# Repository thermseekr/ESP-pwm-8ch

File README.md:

# ESP-PWM-8CH
 
ESP8266/ESP32 based board with 8x PWM output channels.

This board is designed to be driven by an Olimex ESP32-POE, ESP32-POE-ISO or Wemos D1 Mini modules. When using the Wemos D1 Mini the maximum number of outputs is 4, and expect some flickering and frequency oscillation due to the software implementation of the PWMs.

The design considers that the board will be mounted on a PCB DIN rail holder. The dimensions consider the holders offered by the Brazilian manufacturer Metaltex, check [here](https://www.metaltex.com.br/produtos/componentes/suportes/sp7-suporte-para-montagem-de-placa-de-circuito-impresso-em-trilho-din) for details.

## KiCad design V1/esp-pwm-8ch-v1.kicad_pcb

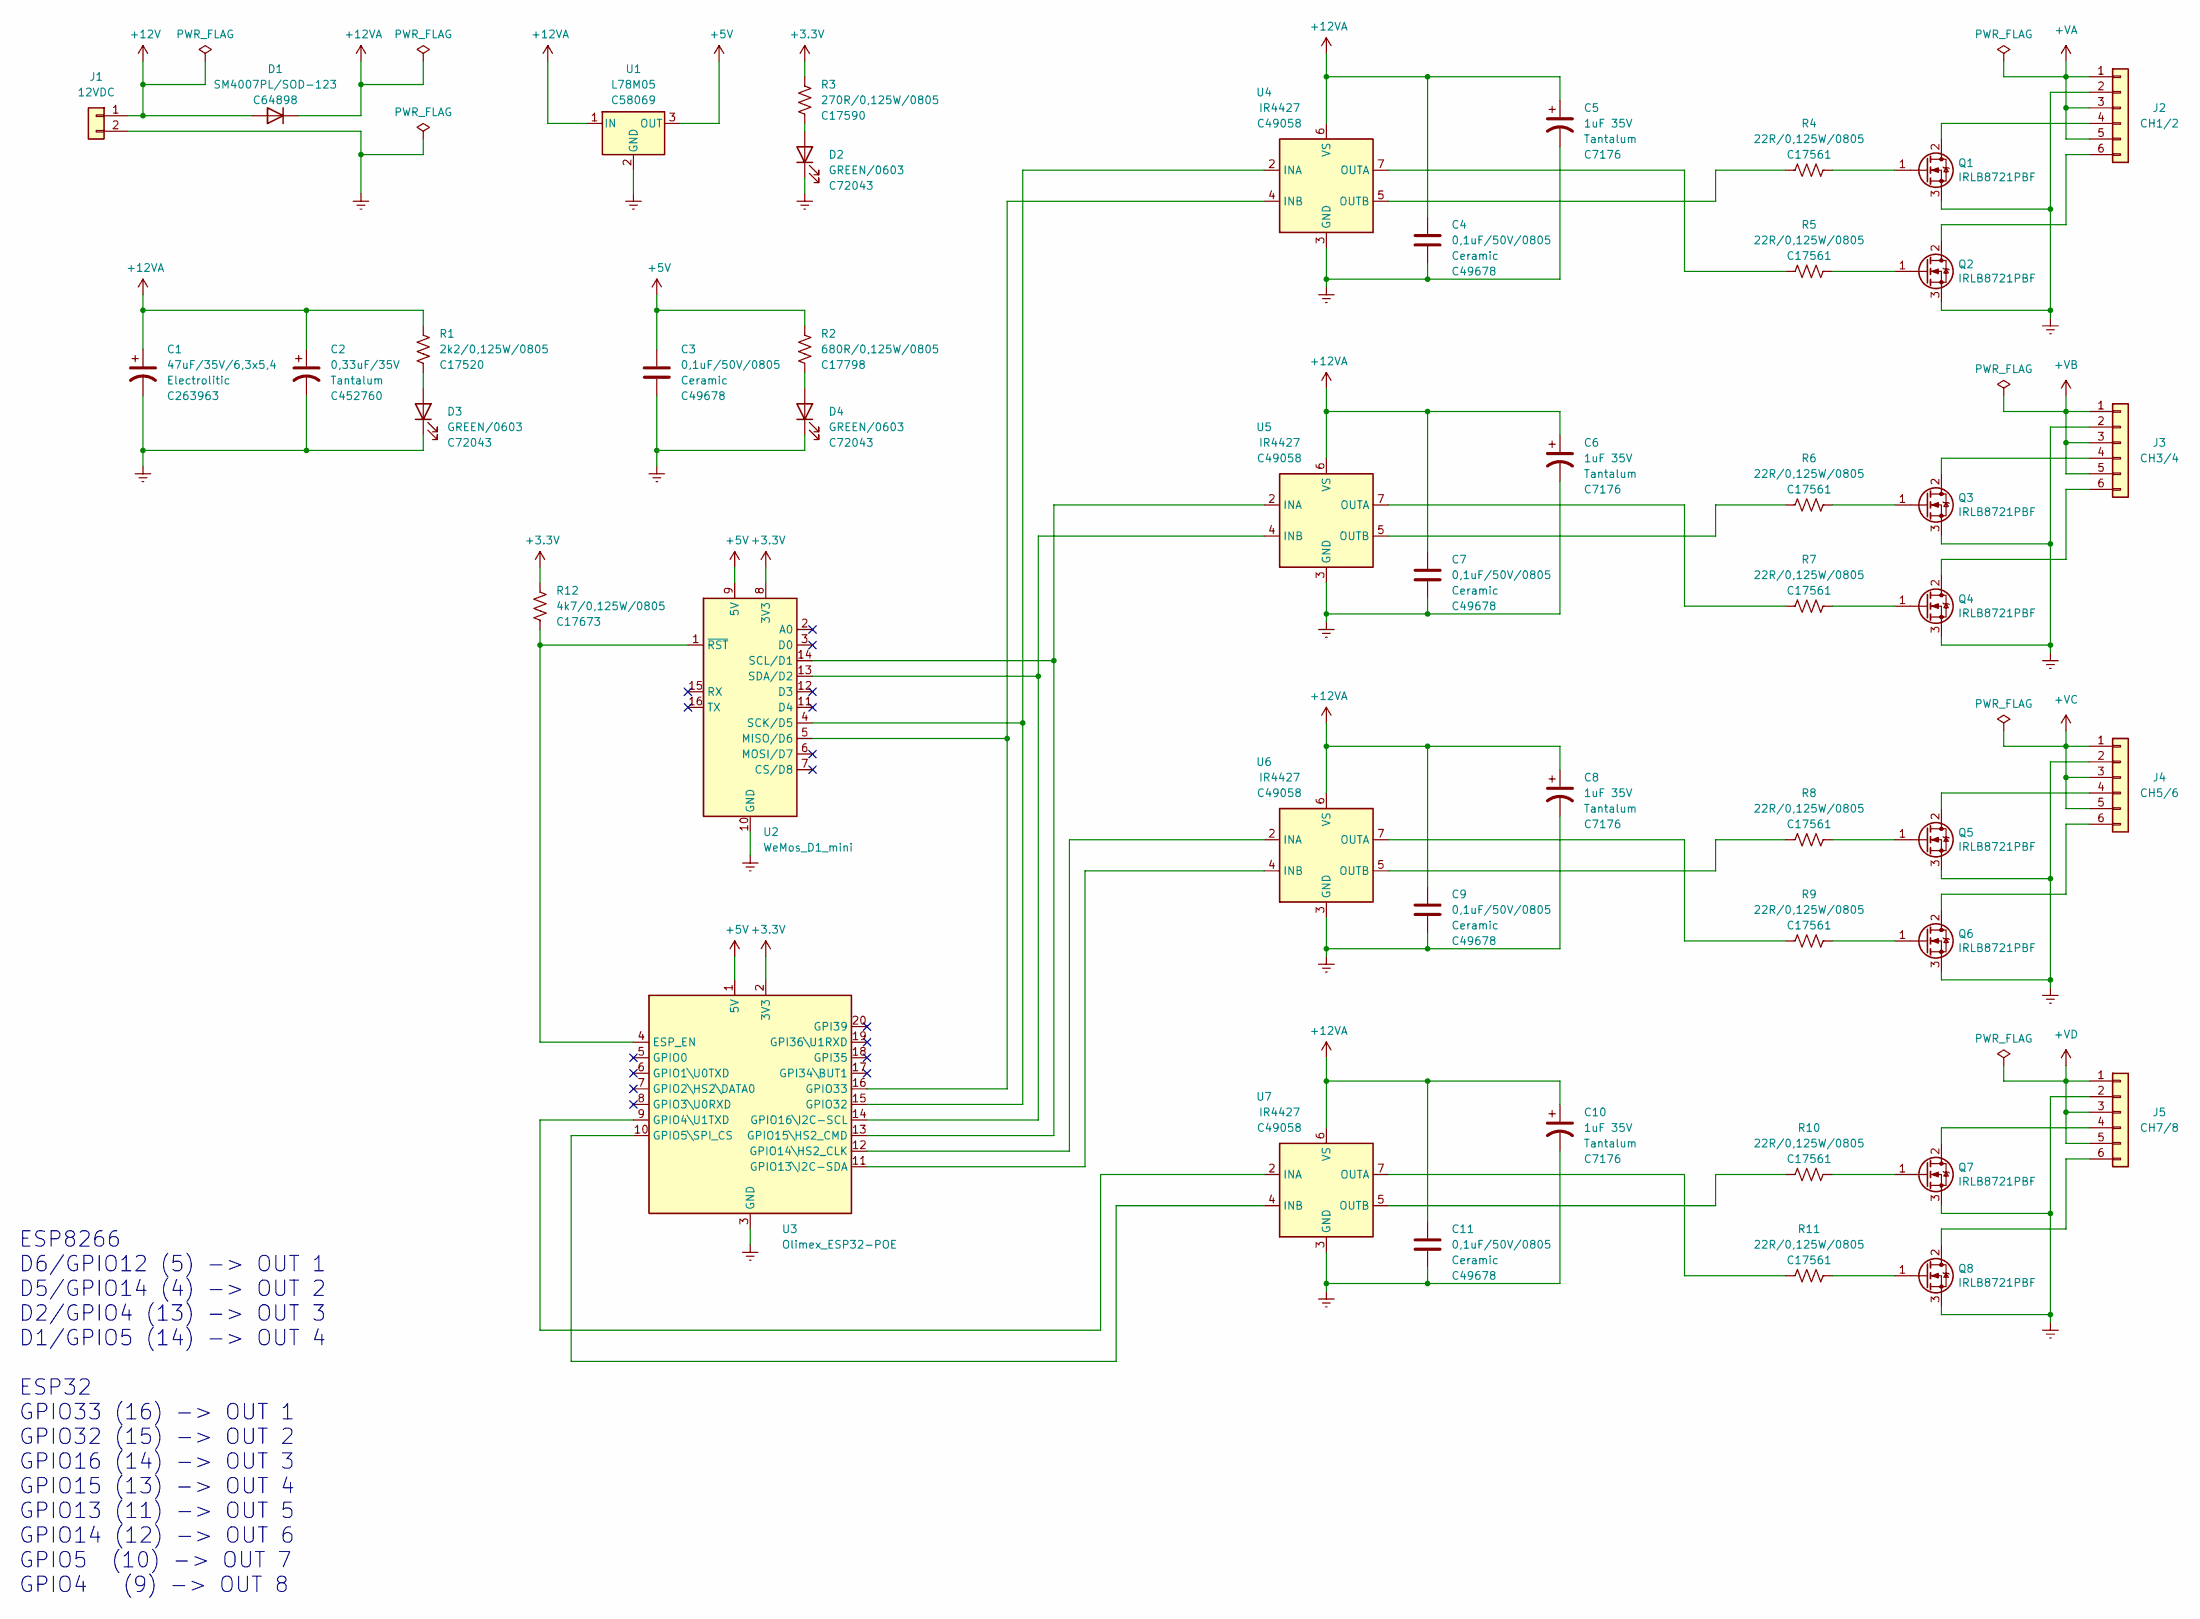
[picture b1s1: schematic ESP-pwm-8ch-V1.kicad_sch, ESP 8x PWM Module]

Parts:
C1: 47uF/35V/6,3x5,4; CP_Elec_6.3x5.4; Mfr PN CK1V470MCRE54; JLCPCB BOM 1
C2: 0,33uF/35V; CP_EIA-3216-18_Kemet-A_Pad1.58x1.35mm_HandSolder; Mfr PN T491A334M035AT; JLCPCB BOM 1
C3, C4, C7, C9, C11: 0,1uF/50V/0805; C_0805_2012Metric; Mfr PN CC0805KRX7R9BB104; JLCPCB BOM 1
C5, C6, C8, C10: 1uF 35V; CP_EIA-3216-18_Kemet-A_Pad1.58x1.35mm_HandSolder; Mfr PN TAJA105K035RNJ; JLCPCB BOM 1
D1: SM4007PL/SOD-123; D_SOD-123; Mfr PN SM4007PL; JLCPCB BOM 1
D2, D3, D4: GREEN/0603; LED_0603_1608Metric; Mfr PN 19-217/GHC-YR1S2/3T; JLCPCB BOM 1
J1: 12VDC; TerminalBlock_Phoenix_MKDS-3-2-5.08_1x02_P5.08mm_Horizontal; Mfr PN BR902V; JLCPCB BOM 0
J2: CH1/2; TerminalBlock_Phoenix_MKDS-3-6-5.08_1x06_P5.08mm_Horizontal; Mfr PN BR902V; JLCPCB BOM 0
J3: CH3/4; TerminalBlock_Phoenix_MKDS-3-6-5.08_1x06_P5.08mm_Horizontal; Mfr PN BR902V; JLCPCB BOM 0
J4: CH5/6; TerminalBlock_Phoenix_MKDS-3-6-5.08_1x06_P5.08mm_Horizontal; Mfr PN BR902V; JLCPCB BOM 0
J5: CH7/8; TerminalBlock_Phoenix_MKDS-3-6-5.08_1x06_P5.08mm_Horizontal; Mfr PN BR902V; JLCPCB BOM 0
Q1, Q2, Q3, Q4, Q5, Q6, Q7, Q8: IRLB8721PBF; TO-220-3_Vertical; Mfr PN IRLB8721PBF; JLCPCB BOM 0
R1: 2k2/0,125W/0805; R_0805_2012Metric; Mfr PN 0805W8F2201T5E; JLCPCB BOM 1
R2: 680R/0,125W/0805; R_0805_2012Metric; Mfr PN 0805W8F6800T5E; JLCPCB BOM 1
R3: 270R/0,125W/0805; R_0805_2012Metric; Mfr PN 0805W8F2700T5E; JLCPCB BOM 1
R4, R5, R6, R7, R8, R9, R10, R11: 22R/0,125W/0805; R_0805_2012Metric; Mfr PN 0805W8F220JT5E; JLCPCB BOM 1
R12: 4k7/0,125W/0805; R_0805_2012Metric; Mfr PN 0805W8F2201T5E; JLCPCB BOM 1
U1: L78M05; TO-252-2; Mfr PN L78M05ABDT-TR; JLCPCB BOM 1
U2: WeMos_D1_mini; WEMOS_D1_mini_light_pads
U3: Olimex_ESP32-POE; Olimex_ESP32-POE_Pads; Mfr PN ESP32-POE; JLCPCB BOM 0
U4, U5, U6, U7: IR4427; SOIC-8_3.9x4.9mm_P1.27mm; Mfr PN IR4427STRPBF; JLCPCB BOM 1

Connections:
+3V3: R3.1, R12.1, U2.8 (3V3), U3.2 (3V3)
+5V: C3.1, R2.1, U1.3 (OUT), U2.9 (5V), U3.1 (5V)
+12V: D1.2 (A), J1.1
+12VA: C1.1, C2.1, C4.1, C5.1, C6.1, C7.1, C8.1, C9.1, C10.1, C11.1, D1.1 (K), R1.1, U1.1 (IN), U4.6 (VS), U5.6 (VS), U6.6 (VS), U7.6 (VS)
+VA: J2.1, J2.3, J2.5
+VB: J3.1, J3.3, J3.5
+VC: J4.1, J4.3, J4.5
+VD: J5.1, J5.3, J5.5
GNDREF: C1.2, C2.2, C3.2, C4.2, C5.2, C6.2, C7.2, C8.2, C9.2, C10.2, C11.2, D2.1 (K), D3.1 (K), D4.1 (K), J1.2, J2.2, J3.2, J4.2, J5.2, Q1.3 (S), Q2.3 (S), Q3.3 (S), Q4.3 (S), Q5.3 (S), Q6.3 (S), Q7.3 (S), Q8.3 (S), U1.2 (GND), U2.10 (GND), U3.3 (GND), U4.3 (GND), U5.3 (GND), U6.3 (GND), U7.3 (GND)
unnamed: D2.2 (A), R3.2
unnamed: D3.2 (A), R1.2
unnamed: D4.2 (A), R2.2
unnamed: J2.4, Q1.2 (D)
unnamed: J2.6, Q2.2 (D)
unnamed: J3.4, Q3.2 (D)
unnamed: J3.6, Q4.2 (D)
unnamed: J4.4, Q5.2 (D)
unnamed: J4.6, Q6.2 (D)
unnamed: J5.4, Q7.2 (D)
unnamed: J5.6, Q8.2 (D)
unnamed: Q1.1 (G), R4.1
unnamed: Q2.1 (G), R5.1
unnamed: Q3.1 (G), R6.1
unnamed: Q4.1 (G), R7.1
unnamed: Q5.1 (G), R8.1
unnamed: Q6.1 (G), R9.1
unnamed: Q7.1 (G), R10.1
unnamed: Q8.1 (G), R11.1
unnamed: R4.2, U4.5 (OUTB)
unnamed: R5.2, U4.7 (OUTA)
unnamed: R6.2, U5.5 (OUTB)
unnamed: R7.2, U5.7 (OUTA)
unnamed: R8.2, U6.5 (OUTB)
unnamed: R9.2, U6.7 (OUTA)
unnamed: R10.2, U7.5 (OUTB)
unnamed: R11.2, U7.7 (OUTA)
unnamed: R12.2, U2.1 (~RST), U3.4 (ESP_EN)
unnamed: U2.4 (SCK/D5), U3.15 (GPIO32), U4.2 (INA)
unnamed: U2.5 (MISO/D6), U3.16 (GPIO33), U4.4 (INB)
unnamed: U2.13 (SDA/D2), U3.14 (GPIO16\I2C-SCL), U5.4 (INB)
unnamed: U2.14 (SCL/D1), U3.13 (GPIO15\HS2_CMD), U5.2 (INA)
unnamed: U3.9 (GPIO4\U1TXD), U7.2 (INA)
unnamed: U3.10 (GPIO5\SPI_CS), U7.4 (INB)
unnamed: U3.11 (GPIO13\I2C-SDA), U6.4 (INB)
unnamed: U3.12 (GPIO14\HS2_CLK), U6.2 (INA)

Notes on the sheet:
ESP8266 D6/GPIO12 (5) -> OUT 1 D5/GPIO14 (4) -> OUT 2 D2/GPIO4 (13) -> OUT 3 D1/GPIO5 (14) -> OUT 4 ESP32 GPIO33 (16) -> OUT 1 GPIO32 (15) -> OUT 2 GPIO16 (14) -> OUT 3 GPIO15 (13) -> OUT 4 GPIO13 (11) -> OUT 5 GPIO14 (12) -> OUT 6 GPIO5 (10) -> OUT 7 GPIO4 (9) -> OUT 8

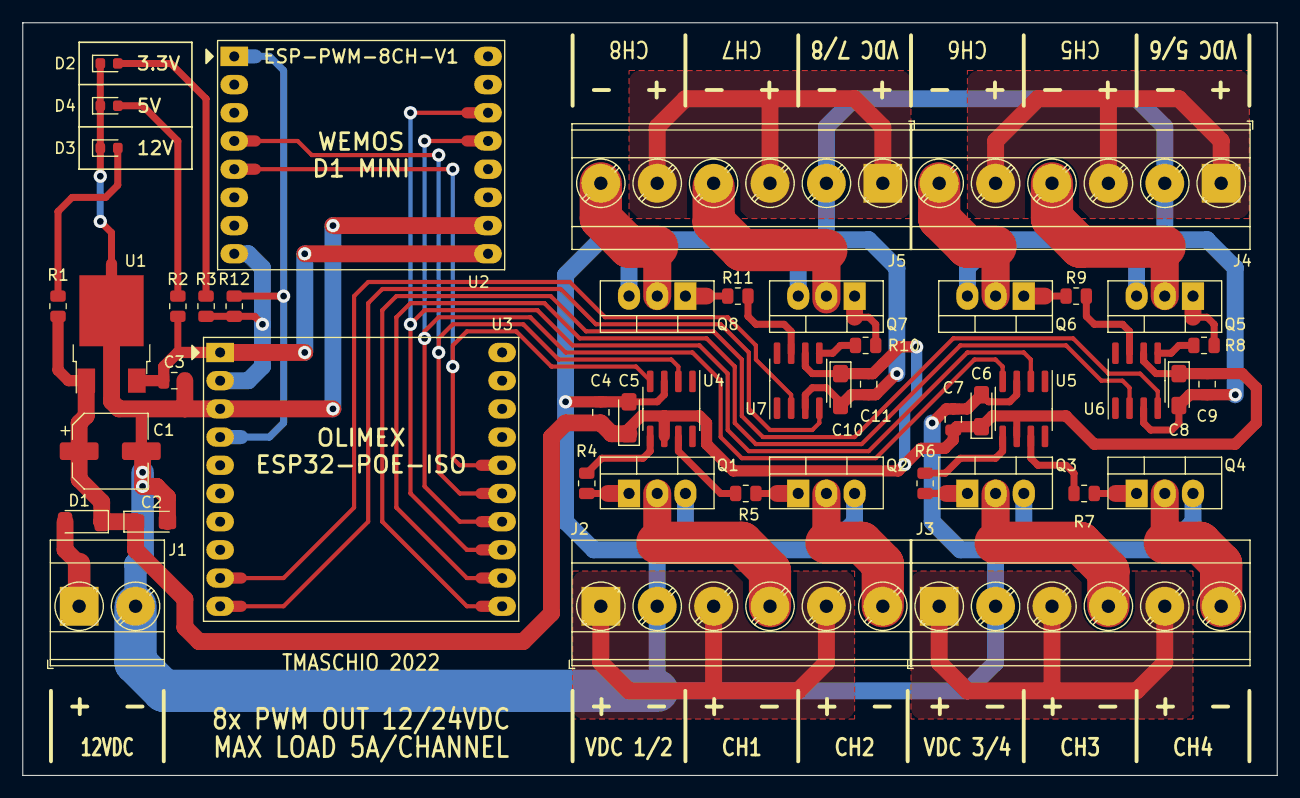
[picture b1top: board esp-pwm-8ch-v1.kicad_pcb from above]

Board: 2 copper layers, 113.0 x 67.8 mm, 47 parts (0 on the bottom side), 45 nets.

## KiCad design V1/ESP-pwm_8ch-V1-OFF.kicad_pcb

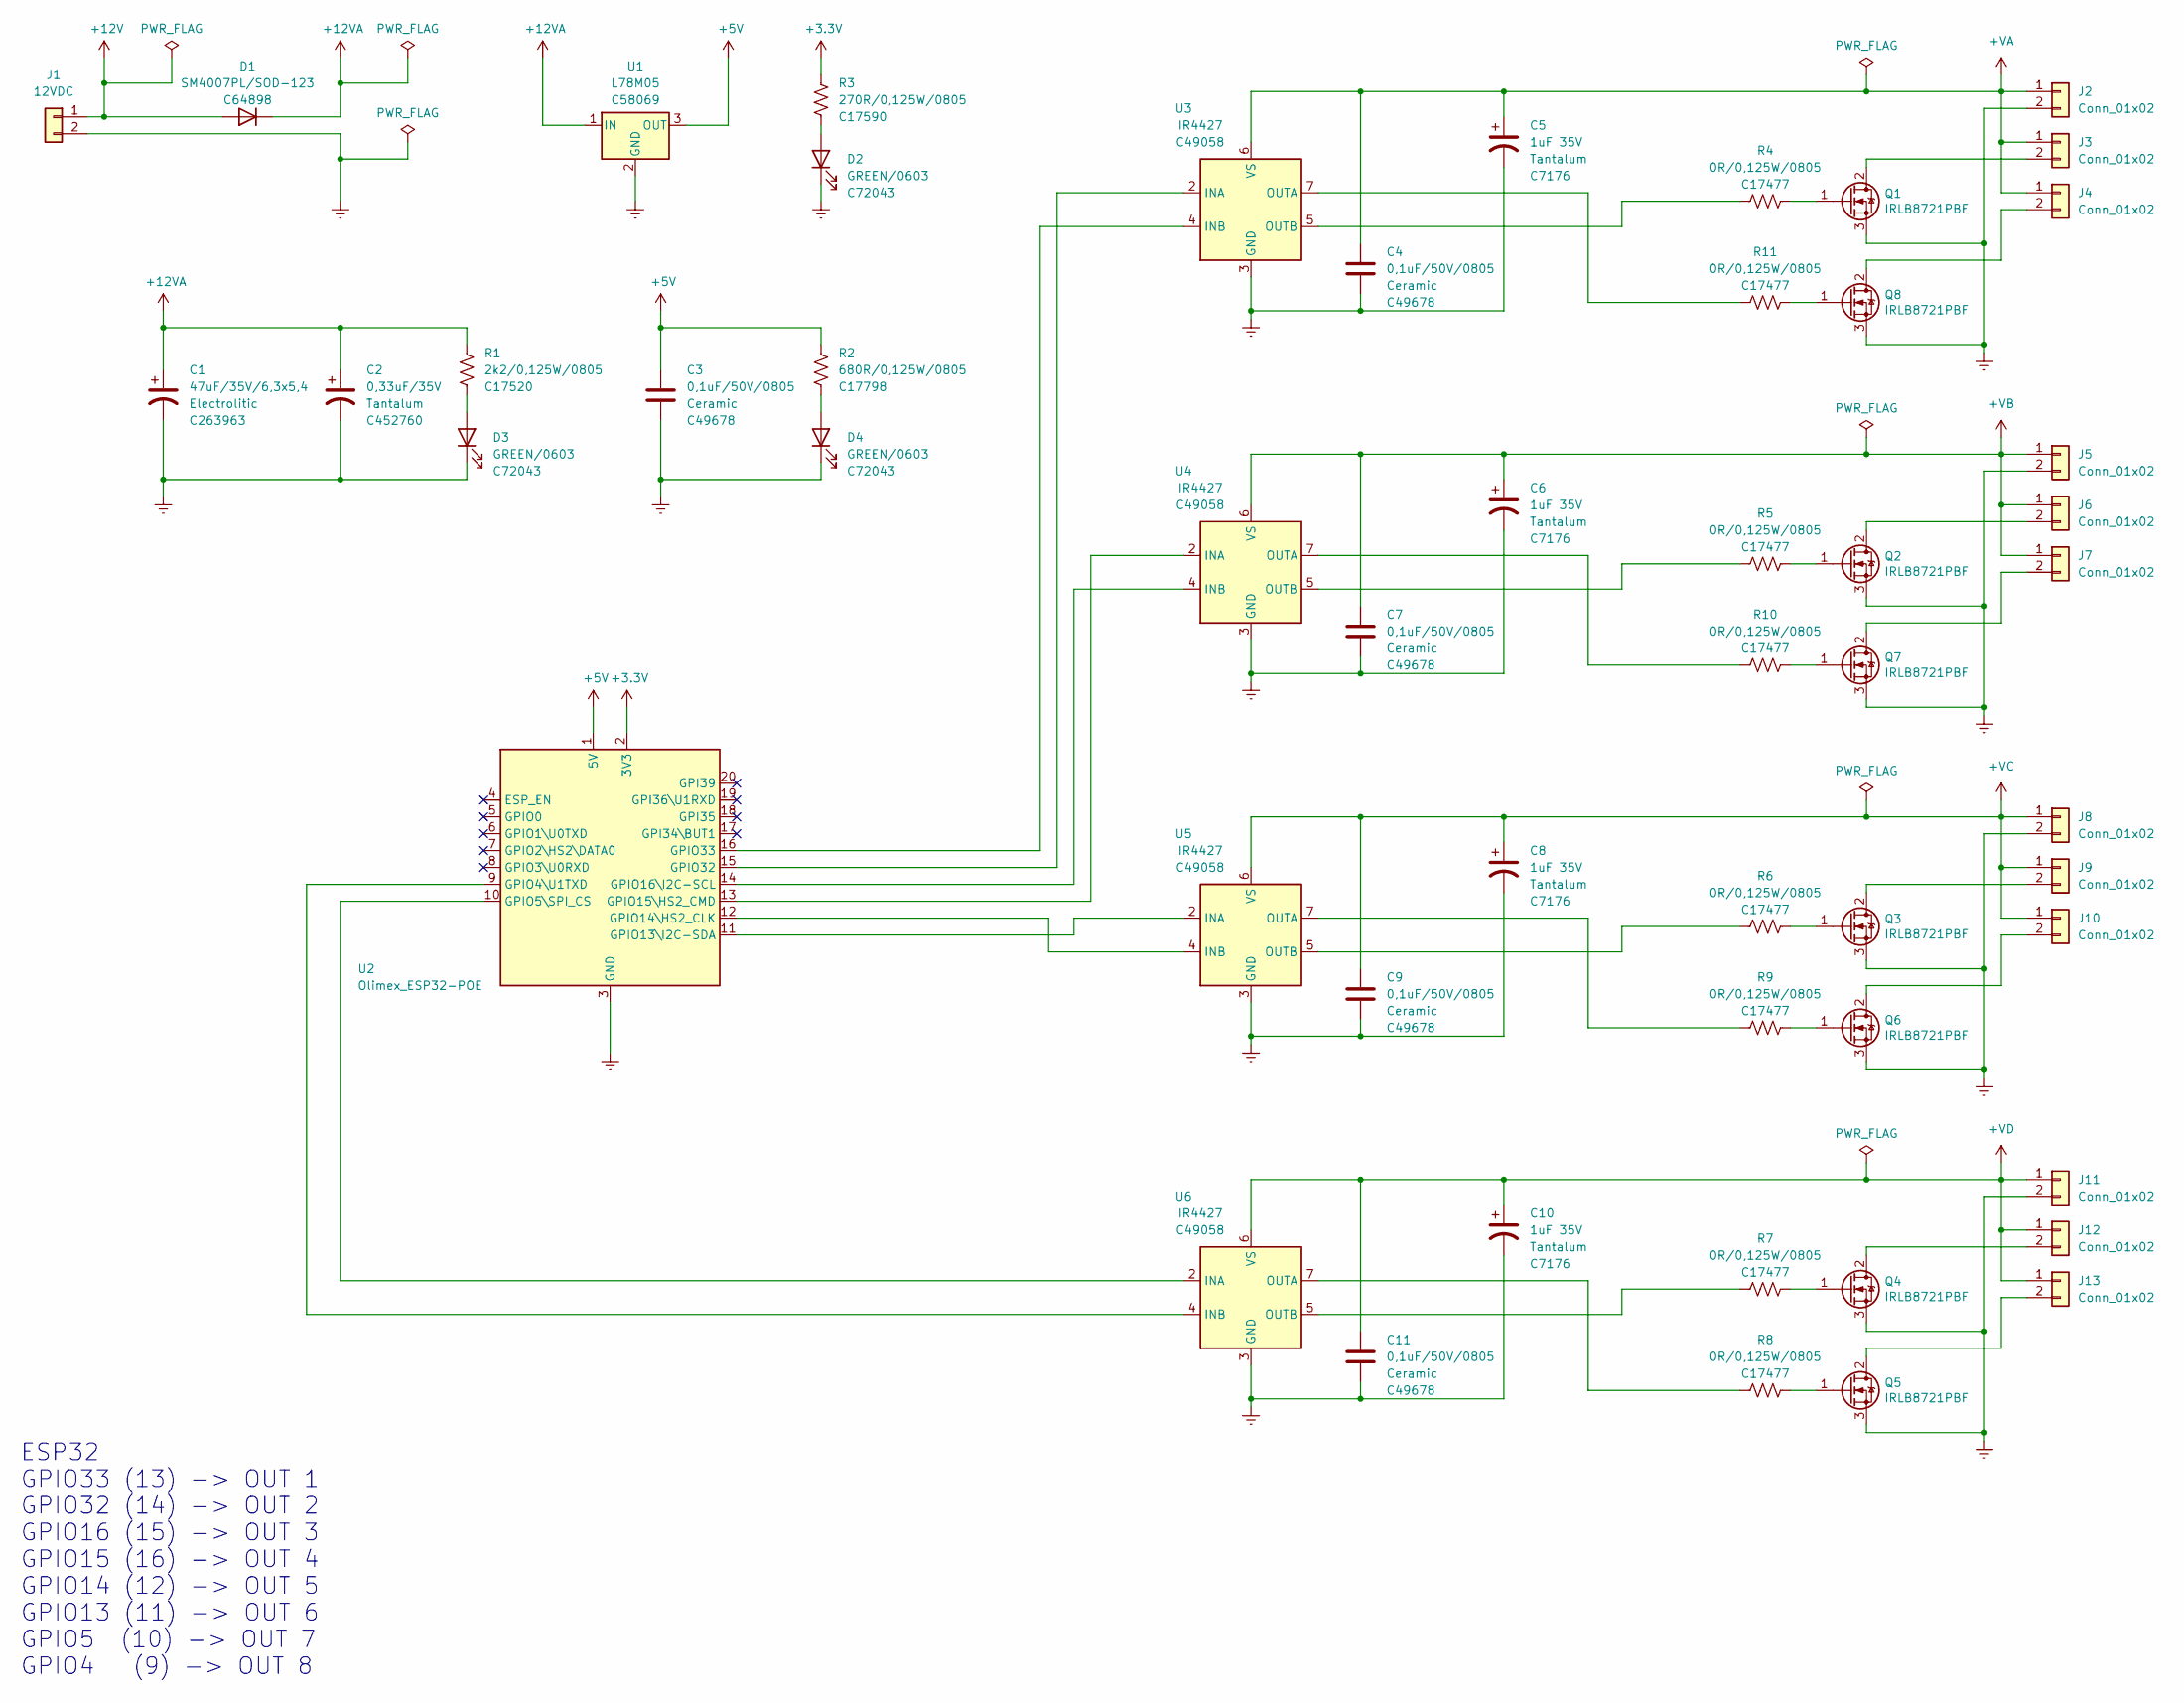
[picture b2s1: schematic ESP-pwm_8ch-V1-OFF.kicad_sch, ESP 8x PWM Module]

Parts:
C1: 47uF/35V/6,3x5,4; CP_Elec_6.3x5.4; Mfr PN CK1V470MCRE54; JLCPCB BOM 1
C2: 0,33uF/35V; CP_EIA-3216-18_Kemet-A; Mfr PN T491A334M035AT; JLCPCB BOM 1
C3, C4, C7, C9, C11: 0,1uF/50V/0805; C_0805_2012Metric; Mfr PN CC0805KRX7R9BB104; JLCPCB BOM 1
C5, C6, C8, C10: 1uF 35V; CP_EIA-3216-18_Kemet-A; Mfr PN TAJA105K035RNJ; JLCPCB BOM 1
D1: SM4007PL/SOD-123; D_SOD-123; Mfr PN SM4007PL; JLCPCB BOM 1
D2, D3, D4: GREEN/0603; LED_0603_1608Metric; Mfr PN 19-217/GHC-YR1S2/3T; JLCPCB BOM 1
J1: 12VDC; TerminalBlock_Phoenix_MKDS-3-2-5.08_1x02_P5.08mm_Horizontal; Mfr PN BR902V; JLCPCB BOM 0
J2, J3, J4, J5, J6, J7, J8, J9, J10, J11, J12, J13: Conn_01x02; TerminalBlock_Phoenix_MKDS-3-2-5.08_1x02_P5.08mm_Horizontal
Q1, Q2, Q3, Q4, Q5, Q6, Q7, Q8: IRLB8721PBF; TO-220-3_Vertical; Mfr PN IRLB8721PBF; JLCPCB BOM 0
R1: 2k2/0,125W/0805; R_0805_2012Metric; Mfr PN 0805W8F2201T5E; JLCPCB BOM 1
R2: 680R/0,125W/0805; R_0805_2012Metric; Mfr PN 0805W8F6800T5E; JLCPCB BOM 1
R3: 270R/0,125W/0805; R_0805_2012Metric; Mfr PN 0805W8F2700T5E; JLCPCB BOM 1
R4, R5, R6, R7, R8, R9, R10, R11: 0R/0,125W/0805; R_0805_2012Metric; Mfr PN 0805W8F0000T5E; JLCPCB BOM 1
U1: L78M05; TO-252-2; Mfr PN L78M05ABDT-TR; JLCPCB BOM 1
U2: Olimex_ESP32-POE; Olimex_ESP32-POE_Pads; Mfr PN ESP32-POE; JLCPCB BOM 0
U3, U4, U5, U6: IR4427; SOIC-8_3.9x4.9mm_P1.27mm; Mfr PN IR4427STRPBF; JLCPCB BOM 1

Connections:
+3V3: R3.1, U2.2 (3V3)
+5V: C3.1, R2.1, U1.3 (OUT), U2.1 (5V)
+12V: D1.2 (A), J1.1
+12VA: C1.1, C2.1, D1.1 (K), R1.1, U1.1 (IN)
+VA: C4.1, C5.1, J2.1, J3.1, J4.1, U3.6 (VS)
+VB: C6.1, C7.1, J5.1, J6.1, J7.1, U4.6 (VS)
+VC: C8.1, C9.1, J8.1, J9.1, J10.1, U5.6 (VS)
+VD: C10.1, C11.1, J11.1, J12.1, J13.1, U6.6 (VS)
GNDREF: C1.2, C2.2, C3.2, C4.2, C5.2, C6.2, C7.2, C8.2, C9.2, C10.2, C11.2, D2.1 (K), D3.1 (K), D4.1 (K), J1.2, J2.2, J5.2, J8.2, J11.2, Q1.3 (S), Q2.3 (S), Q3.3 (S), Q4.3 (S), Q5.3 (S), Q6.3 (S), Q7.3 (S), Q8.3 (S), U1.2 (GND), U2.3 (GND), U3.3 (GND), U4.3 (GND), U5.3 (GND), U6.3 (GND)
unnamed: D2.2 (A), R3.2
unnamed: D3.2 (A), R1.2
unnamed: D4.2 (A), R2.2
unnamed: Q1.1 (G), R4.1
unnamed: J3.2, Q1.2 (D)
unnamed: Q2.1 (G), R5.1
unnamed: J6.2, Q2.2 (D)
unnamed: Q3.1 (G), R6.1
unnamed: J9.2, Q3.2 (D)
unnamed: Q4.1 (G), R7.1
unnamed: J12.2, Q4.2 (D)
unnamed: Q5.1 (G), R8.1
unnamed: J13.2, Q5.2 (D)
unnamed: Q6.1 (G), R9.1
unnamed: J10.2, Q6.2 (D)
unnamed: Q7.1 (G), R10.1
unnamed: J7.2, Q7.2 (D)
unnamed: Q8.1 (G), R11.1
unnamed: J4.2, Q8.2 (D)
unnamed: R4.2, U3.5 (OUTB)
unnamed: R5.2, U4.5 (OUTB)
unnamed: R6.2, U5.5 (OUTB)
unnamed: R7.2, U6.5 (OUTB)
unnamed: R8.2, U6.7 (OUTA)
unnamed: R9.2, U5.7 (OUTA)
unnamed: R10.2, U4.7 (OUTA)
unnamed: R11.2, U3.7 (OUTA)
unnamed: U2.9 (GPIO4\U1TXD), U6.4 (INB)
unnamed: U2.10 (GPIO5\SPI_CS), U6.2 (INA)
unnamed: U2.11 (GPIO13\I2C-SDA), U5.2 (INA)
unnamed: U2.12 (GPIO14\HS2_CLK), U5.4 (INB)
unnamed: U2.13 (GPIO15\HS2_CMD), U4.2 (INA)
unnamed: U2.14 (GPIO16\I2C-SCL), U4.4 (INB)
unnamed: U2.15 (GPIO32), U3.2 (INA)
unnamed: U2.16 (GPIO33), U3.4 (INB)

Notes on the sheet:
ESP32 GPIO33 (13) -> OUT 1 GPIO32 (14) -> OUT 2 GPIO16 (15) -> OUT 3 GPIO15 (16) -> OUT 4 GPIO14 (12) -> OUT 5 GPIO13 (11) -> OUT 6 GPIO5 (10) -> OUT 7 GPIO4 (9) -> OUT 8

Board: 2 copper layers, 53 parts (0 on the bottom side), 44 nets, no tracks yet.

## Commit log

2022-03-29 work in progress
2022-03-29 cleaning up
2022-04-01 Add images
2022-04-01 Update images
2022-04-01 Updated MOSFET gate resistor
2022-04-01 Added ESP8266
2022-04-01 Reset pull up to +3.3V
2022-04-01 Update board images
2022-04-01 PCB tweaks
2022-04-03 rename files to new schema
2022-04-04 Separated driver power lines from loads
2023-05-20 Kicad version update
2023-05-20 Correct icloud erros
2023-08-20 updated connectors
2023-09-06 Rename to lowercase
2024-06-22 Update Kicad version
